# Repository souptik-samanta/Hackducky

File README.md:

# HackDucky - A penetration testing tool.

## What is HackDucky
HackDucky is a compact USB automation and security testing device designed in a small portable form factor. It is inspired by keystroke-injection tools and can emulate a USB keyboard to execute scripted commands automatically when plugged into a computer.The device is powered by a rp2040 and supports payload scripting, making it useful for automation, demonstrations, and authorized penetration testing.
Below is the render of the HackDucky board.

## Why HackDucky
Most devices designed for USB automation or security testing are either expensive, closed-source, or difficult for beginners to modify. We wanted to build something compact, affordable, and easy to experiment with while still being powerful enough for real projects. HackDucky aims to provide a small, portable platform for USB automation, inspired by devices used in security research such as USB Rubber Ducky and other BadUSB-style tools.

Our board is powered by the reliable Raspberry Pi RP2040 microcontroller and includes 16 MB of flash storage, giving plenty of room for scripts and firmware. It also features an SD card slot, allowing users to store and switch between multiple payloads or automation scripts easily. This makes the device flexible for experimentation, demos, and authorized security testing.

HackDucky is designed for a wide range of users. Students can explore how USB HID devices work and learn about hardware security concepts. Makers can use it as a programmable USB automation tool for repetitive tasks. Security enthusiasts can experiment with BadUSB-style techniques in controlled environments, while developers can modify the firmware and hardware to create their own custom tools.

# Features

- RP2040 Microcontroller – Dual-core Arm Cortex-M0+ running at 133 MHz
- 16 MB Flash Storage – Store firmware and large script libraries
- USB-A + USB-C Ports – Flexible connection to different hosts
- MicroSD Card Slot – External storage for payloads and logs
- Led Indicator – Shows device status and script execution
- HID Emulation – Can behave as a keyboard or other USB device
- Script Execution – Run automation scripts automatically
- Open Hardware Design – Fully customizable firmware and PCB
- Compact Portable PCB – Designed for experimentation and hacking

## Getting Started

Your HackDucky ships **without firmware preinstalled**, so you need to flash it before using the board.

### Step 1 — Flash CircuitPython

1. Visit the CircuitPython download page for the RP2040.
2. Download the `.uf2` firmware file.
3. Plug your HackDucky into your computer.
4. A drive named **RPI-RP2** should appear.
5. Drag and drop the `.uf2` file onto the drive.

After flashing, a new drive named **CIRCUITPY** should appear.

---

### Step 2 — Install the Firmware

1. Clone the repository:

```bash
git clone https://github.com/hackclub/hackducky
```
2. Open the repository and navigate to the firmware directory.

3. Copy all files from the firmware folder to the CIRCUITPY drive.

4. Replace existing files if prompted.

5. Delete the existing code.py file.

### Step 3 — Add Your Script

1. Open the ducks folder on the HackDucky drive.

2. Delete any existing files in the folder.

3. Copy your script into the folder with the .ducky extension.

4. Your HackDucky is now ready to run scripts.

```bash
Enjoy ¯\_(ツ)_/¯
```

## Keystroke emulation (wait for video)

<video width="560" height="315" controls>
  <source src="gallery/keystroke.mp4" type="video/mp4">
  Your browser does not support the video tag.
</video>

[Watch on YouTube](https://www.youtube.com/watch?v=__JWsmGk8Tg)

# Team
- @Souptik Samanta
- @Aarav Jham
- @Some1

# Contact
Email Souptik at me@souptik.me(me[at]souptik[dot]me)

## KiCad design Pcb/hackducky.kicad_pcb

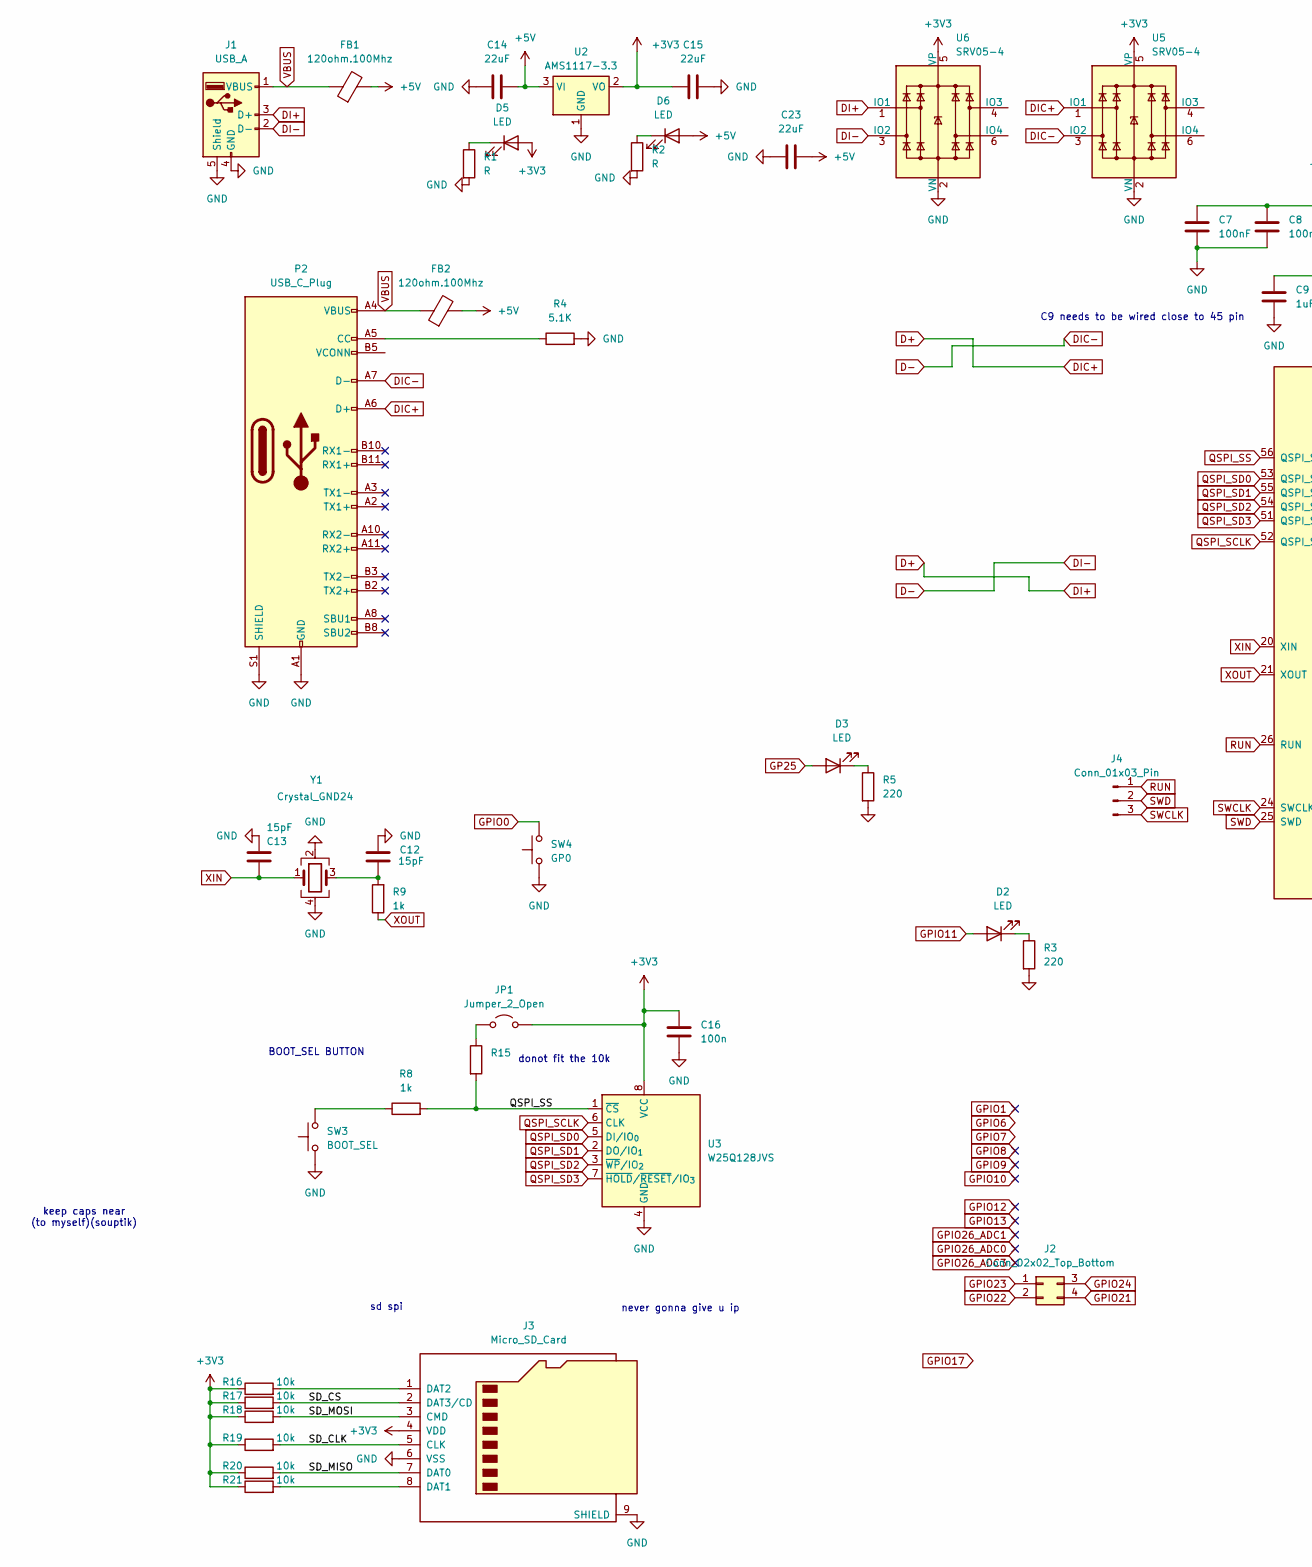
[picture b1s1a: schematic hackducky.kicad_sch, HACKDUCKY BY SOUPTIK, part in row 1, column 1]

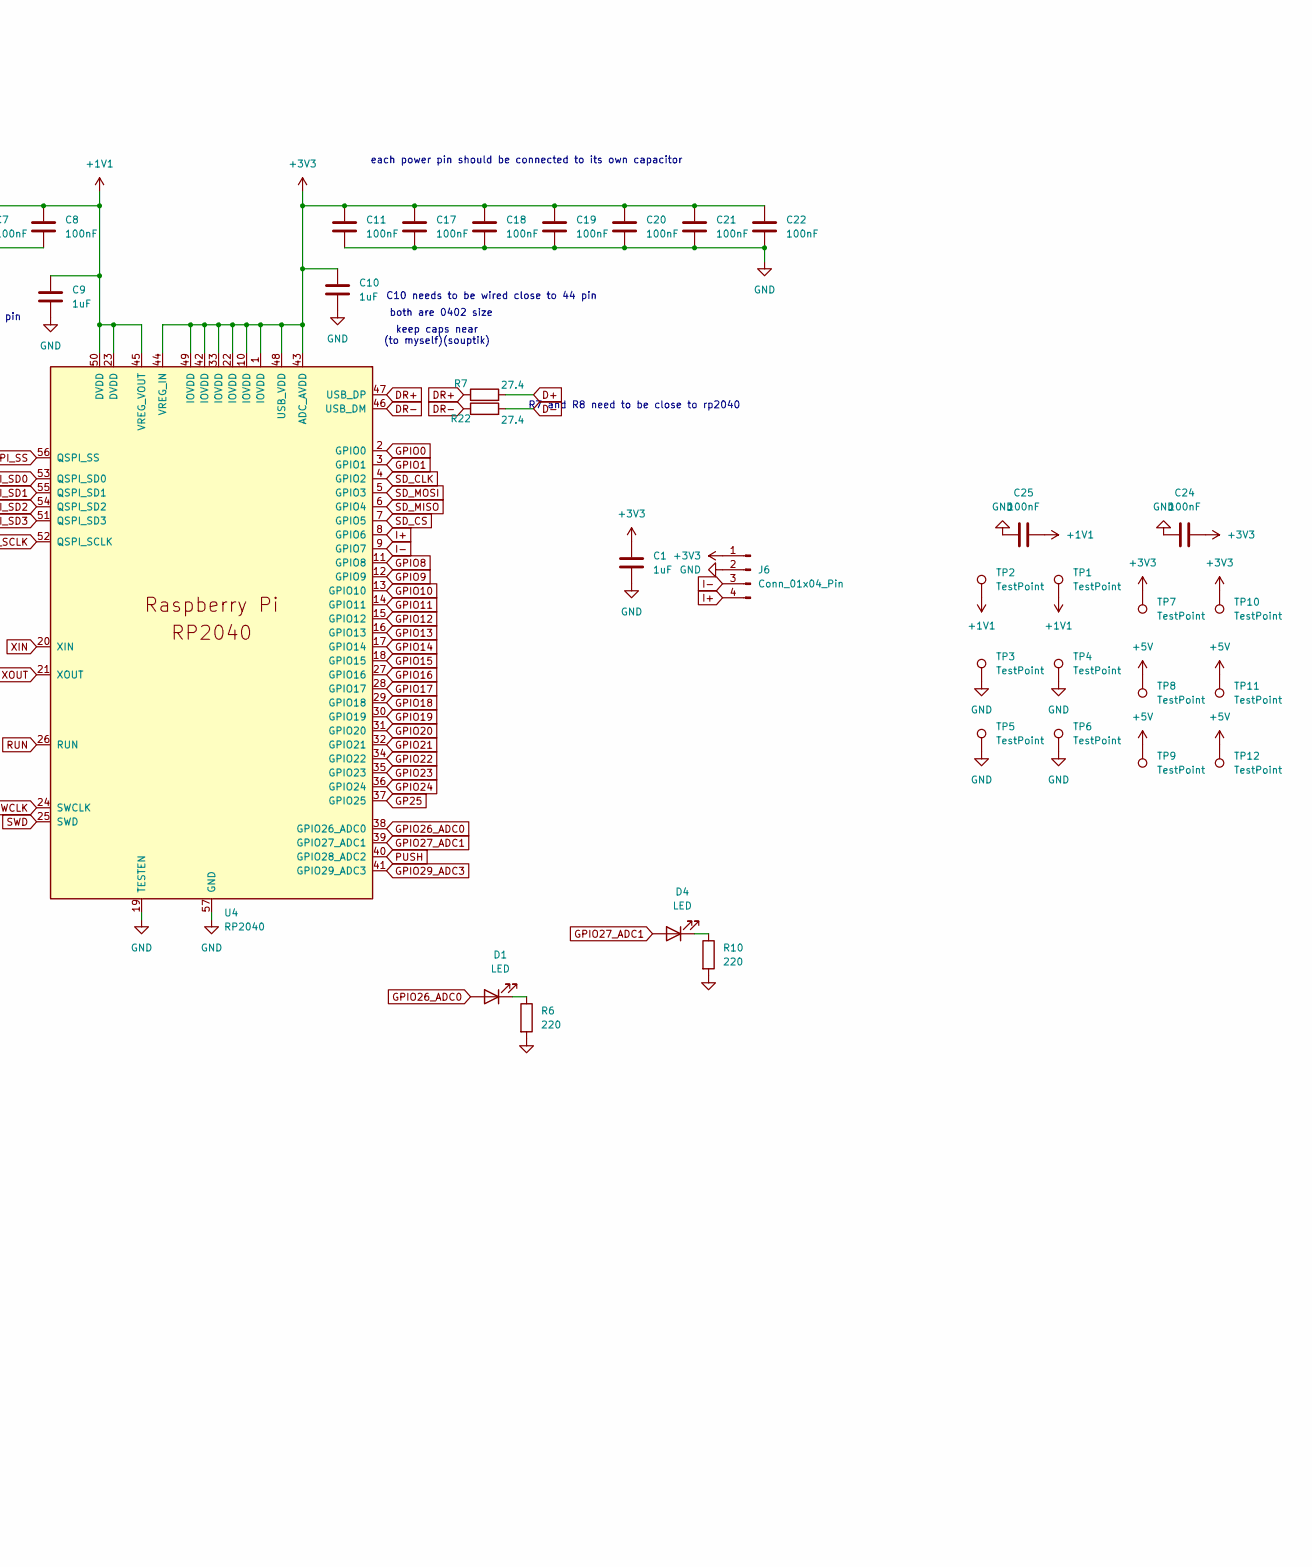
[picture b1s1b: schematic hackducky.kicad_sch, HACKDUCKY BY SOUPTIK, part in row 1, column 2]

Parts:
C1, C9, C10: 1uF; C_0402_1005Metric
C7, C8, C11, C17, C18, C19, C20, C21, C22, C24, C25: 100nF; C_0402_1005Metric
C12, C13: 15pF; C_0402_1005Metric
C14, C15, C23: 22uF; C_0603_1608Metric
C16: 100n; C_0402_1005Metric
D1, D2, D3, D4: LED; LED_0402_1005Metric
D5, D6: LED; LED_0603_1608Metric
FB1, FB2: 120ohm.100Mhz; L_0805_2012Metric
J1: USB_A; USB_A_CNCTech_1001-011-01101_Horizontal
J2: Conn_02x02_Top_Bottom; PinHeader_2x02_P1.00mm_Vertical_SMD
J3: Micro_SD_Card; microSD_HC_Hirose_DM3AT-SF-PEJM5
J4: Conn_01x03_Pin; PinHeader_1x03_P1.27mm_Vertical
J6: Conn_01x04_Pin; PinHeader_1x04_P1.00mm_Vertical
JP1: Jumper_2_Open; SolderJumper-2_P1.3mm_Open_RoundedPad1.0x1.5mm
P2: USB_C_Plug; USB-C-SMD_U261-121N-4BS2S
R1, R2: R; R_0402_1005Metric
R3, R5, R6, R10: 220; R_0402_1005Metric
R4: 5.1K; C_0402_1005Metric
R7, R22: 27.4; R_0402_1005Metric
R8, R9: 1k; R_0402_1005Metric
R15: DNF; R_0402_1005Metric
R16, R17, R18, R19, R20, R21: 10k; R_0402_1005Metric
SW3: BOOT_SEL; SW_Push_SPST_NO_Alps_SKRK; LCSC C318884
SW4: GP0; SW_Push_SPST_NO_Alps_SKRK; LCSC C318884
TP1, TP2, TP3, TP4, TP5, TP6, TP7, TP8, TP9, TP10, TP11, TP12: TestPoint; TestPoint_Pad_D1.0mm
U2: AMS1117-3.3; SOT-223-3_TabPin2
U3: W25Q128JVS; SOIC-8_5.3x5.3mm_P1.27mm
U4: RP2040; QFN-56-1EP_7x7mm_P0.4mm_EP3.2x3.2mm
U5, U6: SRV05-4; SOT-23-6
Y1: Crystal_GND24; Crystal_SMD_Abracon_ABM8G-4Pin_3.2x2.5mm

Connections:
+1V1: C7.1, C8.1, C9.1, C25.2, TP1.1, TP2.1, U4.23 (DVDD), U4.45 (VREG_VOUT), U4.50 (DVDD)
+3V3: C1.1, C10.1, C11.1, C15.2, C16.1, C17.1, C18.1, C19.1, C20.1, C21.1, C22.1, C24.2, D5.2 (A), J3.4 (VDD), J6.1, JP1.2 (B), R16.1, R17.1, R18.1, R19.1, R20.1, R21.1, TP7.1, TP10.1, U2.2 (VO), U3.8 (VCC), U4.1 (IOVDD), U4.10 (IOVDD), U4.22 (IOVDD), U4.33 (IOVDD), U4.42 (IOVDD), U4.43 (ADC_AVDD), U4.44 (VREG_IN), U4.48 (USB_VDD), U4.49 (IOVDD), U5.5 (VP), U6.5 (VP)
+5V: C14.1, C23.1, D6.2 (A), FB1.2, FB2.2, TP8.1, TP9.1, TP11.1, TP12.1, U2.3 (VI)
D+: J1.3 (D+), P2.A6 (D+), R7.2, U5.1 (IO1), U6.1 (IO1)
D-: J1.2 (D-), P2.A7 (D-), R22.2, U5.3 (IO2), U6.3 (IO2)
DR+: R7.1, U4.47 (USB_DP)
DR-: R22.1, U4.46 (USB_DM)
GND: C1.2, C7.2, C8.2, C9.2, C10.2, C11.2, C12.2, C13.2, C14.2, C15.1, C16.2, C17.2, C18.2, C19.2, C20.2, C21.2, C22.2, C23.2, C24.1, C25.1, J1.4 (GND), J1.5 (Shield), J3.6 (VSS), J3.9 (SHIELD), J6.2, P2.A1 (GND), P2.A12 (GND), P2.B1 (GND), P2.B12 (GND), P2.S1 (SHIELD), R1.2, R2.2, R3.2, R4.2, R5.2, R6.2, R10.2, SW3.1, SW4.1, TP3.1, TP4.1, TP5.1, TP6.1, U2.1 (GND), U3.4 (GND), U4.19 (TESTEN), U4.57 (GND), U5.2 (VN), U6.2 (VN), Y1.2, Y1.4
GP25: D3.2 (A), U4.37 (GPIO25)
GPIO0: SW4.2, U4.2 (GPIO0)
GPIO1: U4.3 (GPIO1)
GPIO8: U4.11 (GPIO8)
GPIO9: U4.12 (GPIO9)
GPIO10: U4.13 (GPIO10)
GPIO11: D2.2 (A), U4.14 (GPIO11)
GPIO12: U4.15 (GPIO12)
GPIO13: U4.16 (GPIO13)
GPIO14: U4.17 (GPIO14)
GPIO15: U4.18 (GPIO15)
GPIO16: U4.27 (GPIO16)
GPIO17: U4.28 (GPIO17)
GPIO18: U4.29 (GPIO18)
GPIO19: U4.30 (GPIO19)
GPIO20: U4.31 (GPIO20)
GPIO21: J2.4, U4.32 (GPIO21)
GPIO22: J2.2, U4.34 (GPIO22)
GPIO23: J2.1, U4.35 (GPIO23)
GPIO24: J2.3, U4.36 (GPIO24)
GPIO26_ADC0: D1.2 (A), U4.38 (GPIO26_ADC0)
GPIO27_ADC1: D4.2 (A), U4.39 (GPIO27_ADC1)
GPIO29_ADC3: U4.41 (GPIO29_ADC3)
I+: J6.4, U4.8 (GPIO6)
I-: J6.3, U4.9 (GPIO7)
unnamed: C12.1, R9.2, Y1.3
unnamed: D1.1 (K), R6.1
unnamed: D2.1 (K), R3.1
unnamed: D3.1 (K), R5.1
unnamed: D4.1 (K), R10.1
unnamed: D5.1 (K), R1.1
unnamed: D6.1 (K), R2.1
unnamed: J3.8 (DAT1), R21.2
unnamed: J3.1 (DAT2), R16.2
unnamed: JP1.1 (A), R15.1
unnamed: P2.A5 (CC), R4.1
unnamed: R8.1, SW3.2
PUSH: U4.40 (GPIO28_ADC2)
QSPI_SCLK: U3.6 (CLK), U4.52 (QSPI_SCLK)
QSPI_SD0: U3.5 (DI/IO_{0}), U4.53 (QSPI_SD0)
QSPI_SD1: U3.2 (DO/IO_{1}), U4.55 (QSPI_SD1)
QSPI_SD2: U3.3 (~WP/IO_{2}), U4.54 (QSPI_SD2)
QSPI_SD3: U3.7 (~HOLD/~RESET/IO_{3}), U4.51 (QSPI_SD3)
QSPI_SS: R8.2, R15.2, U3.1 (~CS), U4.56 (QSPI_SS)
RUN: J4.1, U4.26 (RUN)
SD_CLK: J3.5 (CLK), R19.2, U4.4 (GPIO2)
SD_CS: J3.2 (DAT3/CD), R17.2, U4.7 (GPIO5)
SD_MISO: J3.7 (DAT0), R20.2, U4.6 (GPIO4)
SD_MOSI: J3.3 (CMD), R18.2, U4.5 (GPIO3)
SWCLK: J4.3, U4.24 (SWCLK)
SWD: J4.2, U4.25 (SWD)
VBUS: FB1.1, FB2.1, J1.1 (VBUS), P2.A4 (VBUS), P2.A9 (VBUS), P2.B4 (VBUS), P2.B9 (VBUS)
XIN: C13.1, U4.20 (XIN), Y1.1
XOUT: R9.1, U4.21 (XOUT)

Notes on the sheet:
sd spi
C9 needs to be wired close to 45 pin
keep caps near (to myself)(souptik)
donot fit the 10k
R7 and R8 need to be close to rp2040
C10 needs to be wired close to 44 pin
BOOT_SEL BUTTON
never gonna give u ip
both are 0402 size
each power pin should be connected to its own capacitor

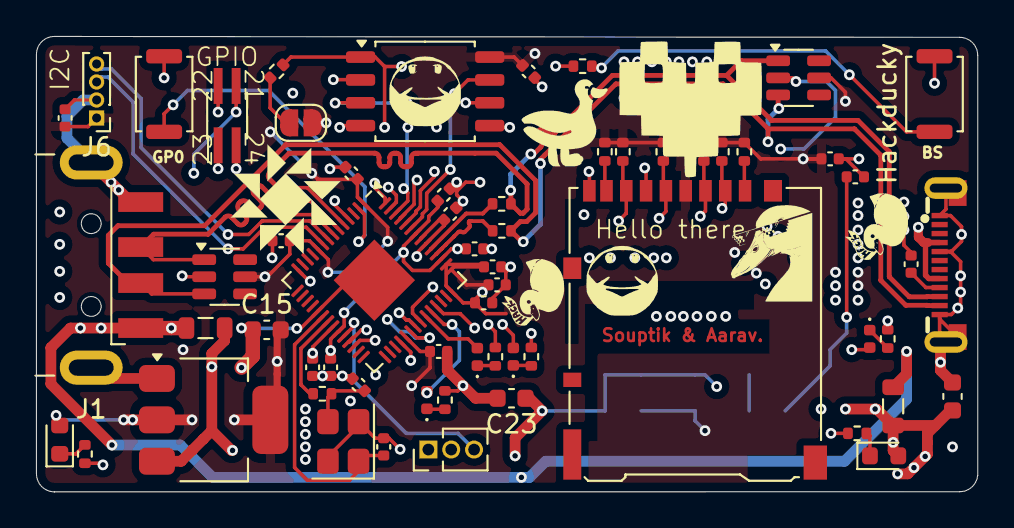
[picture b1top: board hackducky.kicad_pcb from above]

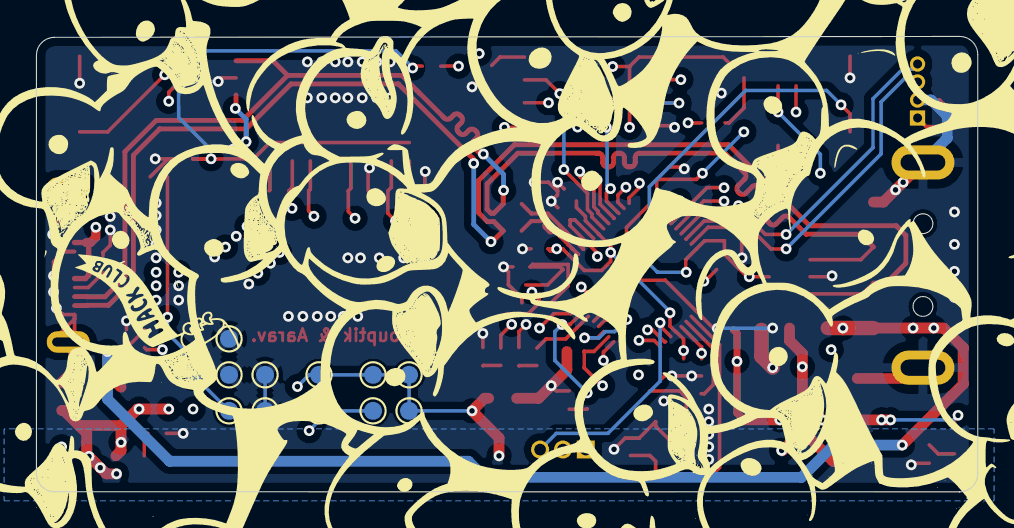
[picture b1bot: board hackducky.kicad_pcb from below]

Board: 4 copper layers, 52.3 x 25.3 mm, 73 parts (12 on the bottom side), 47 nets.

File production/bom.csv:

Designator,Footprint,Quantity,Value,LCSC Part #
"C10, C14, C9",402,3,1uF,C14445
"C11, C17, C18, C19, C20, C21, C7, C8",402,8,100nF,C513772
"C12, C13",402,2,15pF,C106997
C15,805,1,1uF,C516002
"C16, C22",402,2,100n,C513772
"D1, D4",LED_WS2812B-2020_PLCC4_2.0x2.0mm,2,WS2812B,C965555
"D2, D3",D_SOD-123F,2,MBR1020VL,C191986
J1,USB_A_CNCTech_1001-011-01101_Horizontal,1,USB_A,c136453
J2,PinHeader_2x02_P1.00mm_Vertical_SMD,1,Conn_02x02_Top_Bottom,
J3,microSD_HC_Molex_47219-2001,1,Micro_SD_Card,C114218
P2,USB_C_Plug_Molex_105444,1,USB_C_Plug,C3151751
R15,805,1,DNF,
"R16, R17, R18, R19, R20, R21",402,6,10k,C844098
"R22, R7",402,2,27.4,C2076786
"R4, R5",402,2,5.1K,C159990
R6,805,1,5.1K,C2085709
"R8, R9",402,2,1k,C242161
"SW3, SW4",SW_Push_SPST_NO_Alps_SKRK,2,BOOT_SEL,C318884
U1,SOIC-8_5.3x5.3mm_P1.27mm,1,W25Q16JVSS,C131025
U2,SOT-23-5,1,AP2112K-3.3,C23380830
"U3, U5",SOT-666,2,USBLC6-2P6,C15999
U4,QFN-56-1EP_7x7mm_P0.4mm_EP3.2x3.2mm,1,RP2040,RP2040
Y1,Crystal_SMD_Abracon_ABM8G-4Pin_3.2x2.5mm,1,Crystal_GND24,C133334

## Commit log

2025-04-06 Initial commit of KiCad project
2025-04-06 second
2025-04-07 sch done
2025-04-07 schm done fl
2025-04-08 schm full done
2025-04-08 pcb layout
2025-04-13 pcb some few little
2025-04-13 did pcb a lil bit
2025-04-17 pcb work
2025-04-18 did pcb most of work done wooo
2025-04-18 lets end stream here eh done with qspi and sd so yea https://youtu.be/rrAUqN_xz0k
2025-04-19 full done yayayay
2025-04-19 gerber/zip
2025-04-19 gerber
2025-04-19 done beter
2025-04-20 bom fix
2025-04-20 will do pr latr
2025-04-20 fixed silkscreen
2025-05-09 v4 mostly tuned paths
2025-05-09 add sk6812 model
2025-05-13 v4 done
2025-05-13 silkscreen
2025-05-13 added readme and photos:
2025-05-13 readme fix
2025-05-13 pic fix
2025-05-13 fixc
2025-05-13 fix again
2025-05-13 fix again noo
2025-05-13 finish finally hell yeah(mostly :pf:)
2025-05-14 done
2025-05-14 new sm fic
2025-05-14 fixed silkscren
2025-05-18 with bom corrected
2025-05-20 new_
2025-05-30 done ig
2025-06-07 done:
2025-06-08 sob fix gertber
2025-07-03 2nd v
2025-07-24 I am done
2025-08-09 final done with calip
2025-09-10 again lol
2026-03-12 POLISH
2026-03-12 readmefix
2026-03-12 Add video and fix readme
2026-03-12 Video display
2026-03-12 Readme
